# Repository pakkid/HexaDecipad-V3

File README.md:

# HexaDecipad-V3

**HexaDecipad-V3** is a custom-designed macropad built for **[Hack Club Stardance](https://stardance.hackclub.com/)**—a summer engineering program run by Hack Club in partnership with NASA, AMD, and GitHub. 

After running into some issues with the previous versions, Version 3 is redesigned from the ground up to be reliable and highly functional!

---

## Hardware Features

- **Microcontroller:** Seeed Studio XIAO (compatible with XIAO RP2040, SAMD21, etc.)
- **Keys:** 10x Cherry MX-compatible hotswap sockets (using `MX100H` footprints)
- **Rotary Encoders:** 2x Alps EC11-style rotary encoders with integrated push switches
- **Key Matrix Diodes:** 12x 1N4148 through-hole diodes (`DO-35` package)
- **PCB Design:** Fully designed in KiCad (files located in the `PCB/` directory)

---

## Repository Structure

- [`PCB/`](file:///home/pakkid/Documents/GitHub/HexaDecipad-V3/PCB/) — KiCad schematic (`.kicad_sch`), PCB layout (`.kicad_pcb`), and libraries.
- [`LICENSE`](file:///home/pakkid/Documents/GitHub/HexaDecipad-V3/LICENSE) — MIT License.

---

## Stardance YSWS
This project was shipped as part of **Hack Club's Stardance YSWS** ("You Ship, We Ship")

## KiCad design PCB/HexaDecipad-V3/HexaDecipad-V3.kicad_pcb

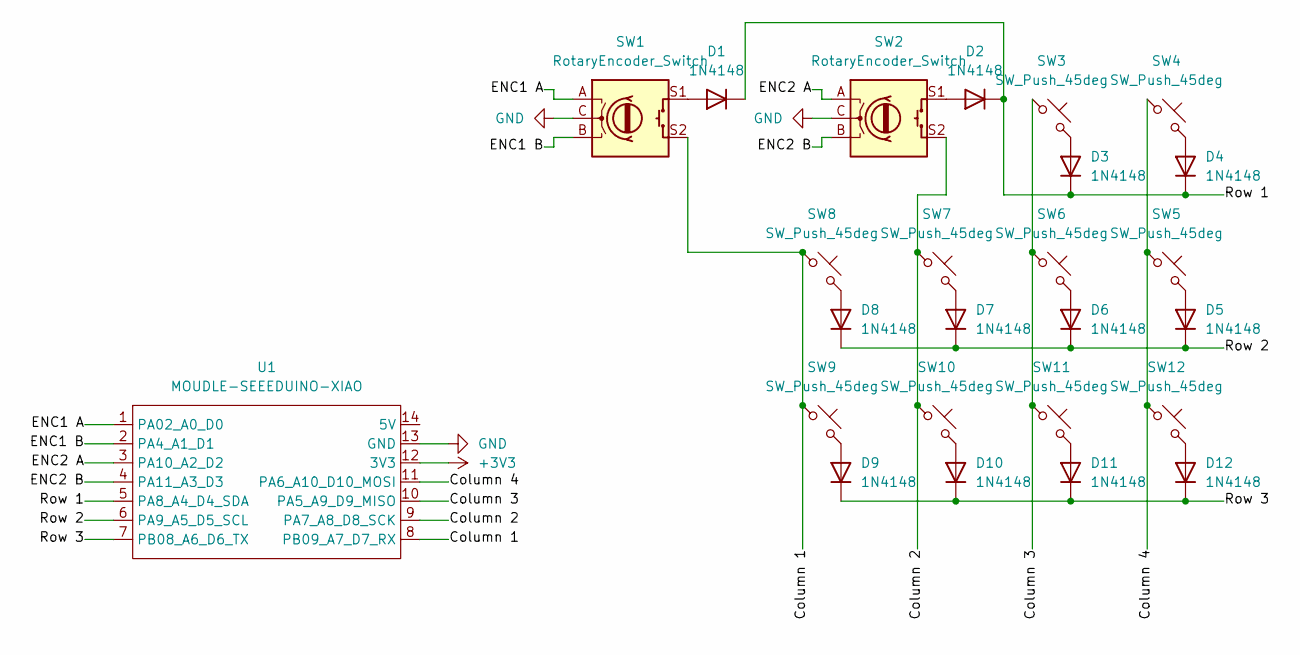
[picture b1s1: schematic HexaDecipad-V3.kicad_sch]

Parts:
D1, D2, D3, D4, D5, D6, D7, D8, D9, D10, D11, D12: 1N4148; D_DO-35_SOD27_P7.62mm_Horizontal
SW1, SW2: RotaryEncoder_Switch; RotaryEncoder_Alps_EC11E-Switch_Vertical_H20mm
SW3, SW4, SW5, SW6, SW7, SW8, SW9, SW10, SW11, SW12: SW_Push_45deg; MX100H
U1: MOUDLE-SEEEDUINO-XIAO; XIAO-Generic-Hybrid-14P-2.54-21X17.8MM

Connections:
+3V3: U1.12 (3V3)
/Column 1: SW1.S2, SW8.1, SW9.1, U1.8 (PB09_A7_D7_RX)
/Column 2: SW2.S2, SW7.1, SW10.1, U1.9 (PA7_A8_D8_SCK)
/Column 3: SW3.1, SW6.1, SW11.1, U1.10 (PA5_A9_D9_MISO)
/Column 4: SW4.1, SW5.1, SW12.1, U1.11 (PA6_A10_D10_MOSI)
/ENC1 A: SW1.A, U1.1 (PA02_A0_D0)
/ENC1 B: SW1.B, U1.2 (PA4_A1_D1)
/ENC2 A: SW2.A, U1.3 (PA10_A2_D2)
/ENC2 B: SW2.B, U1.4 (PA11_A3_D3)
/Row 1: D1.1 (K), D2.1 (K), D3.1 (K), D4.1 (K), U1.5 (PA8_A4_D4_SDA)
/Row 2: D5.1 (K), D6.1 (K), D7.1 (K), D8.1 (K), U1.6 (PA9_A5_D5_SCL)
/Row 3: D9.1 (K), D10.1 (K), D11.1 (K), D12.1 (K), U1.7 (PB08_A6_D6_TX)
GND: SW1.C, SW2.C, U1.13 (GND)
unnamed: D1.2 (A), SW1.S1
unnamed: D2.2 (A), SW2.S1
unnamed: D3.2 (A), SW3.2
unnamed: D4.2 (A), SW4.2
unnamed: D5.2 (A), SW5.2
unnamed: D6.2 (A), SW6.2
unnamed: D7.2 (A), SW7.2
unnamed: D8.2 (A), SW8.2
unnamed: D9.2 (A), SW9.2
unnamed: D10.2 (A), SW10.2
unnamed: D11.2 (A), SW11.2
unnamed: D12.2 (A), SW12.2

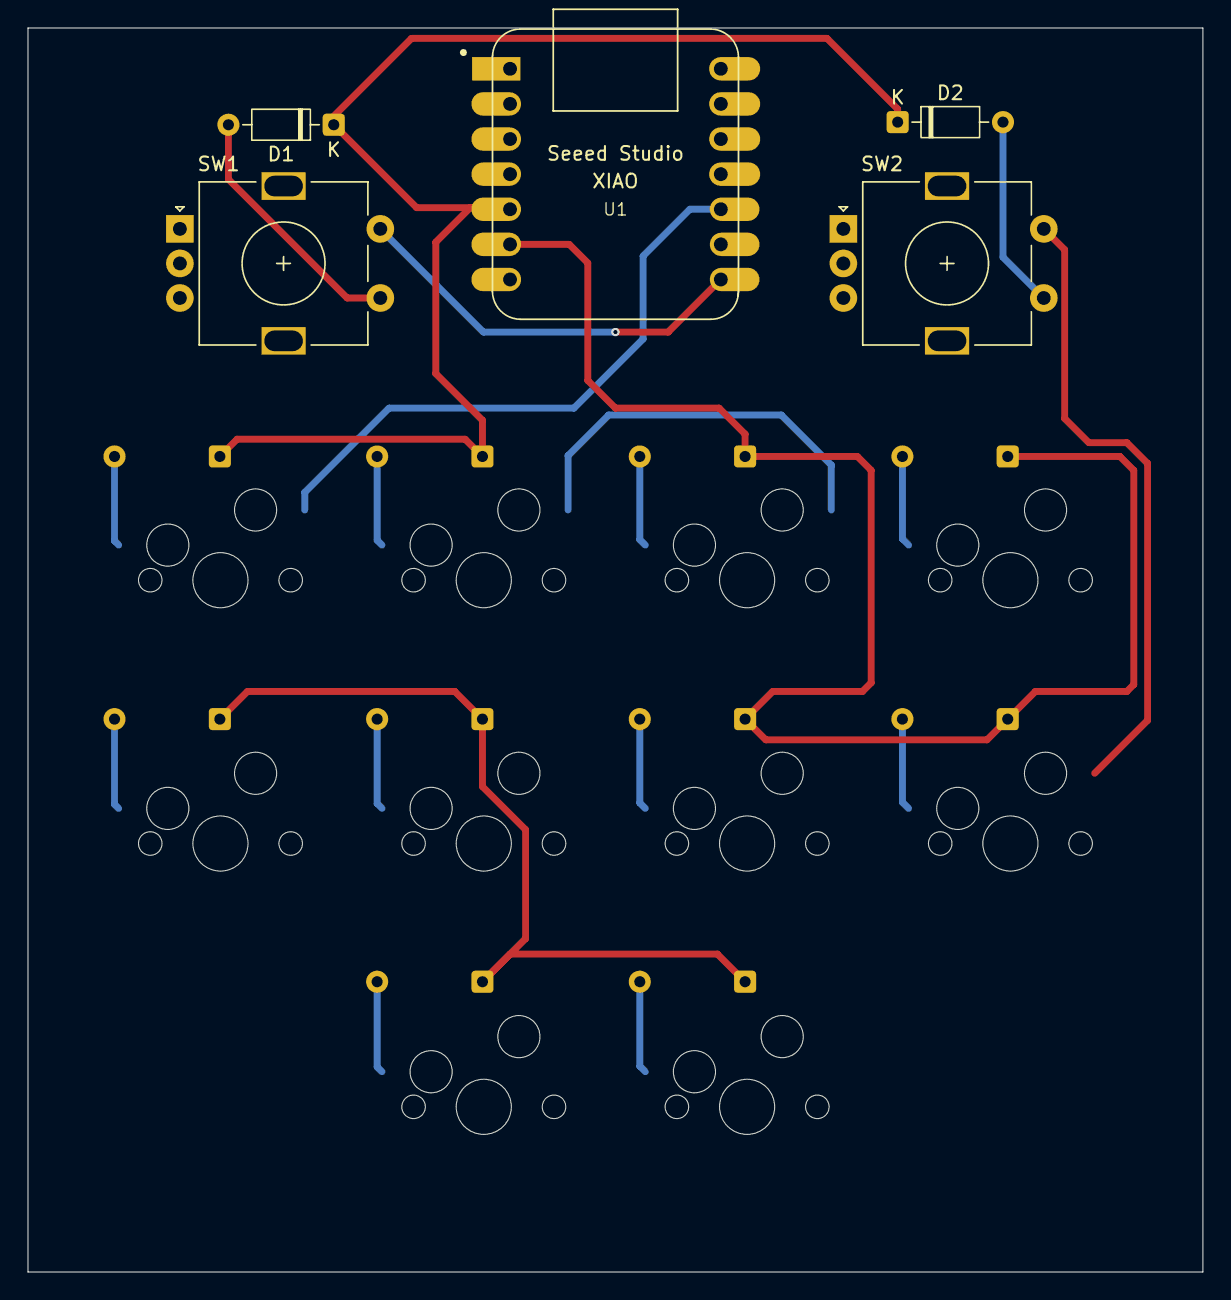
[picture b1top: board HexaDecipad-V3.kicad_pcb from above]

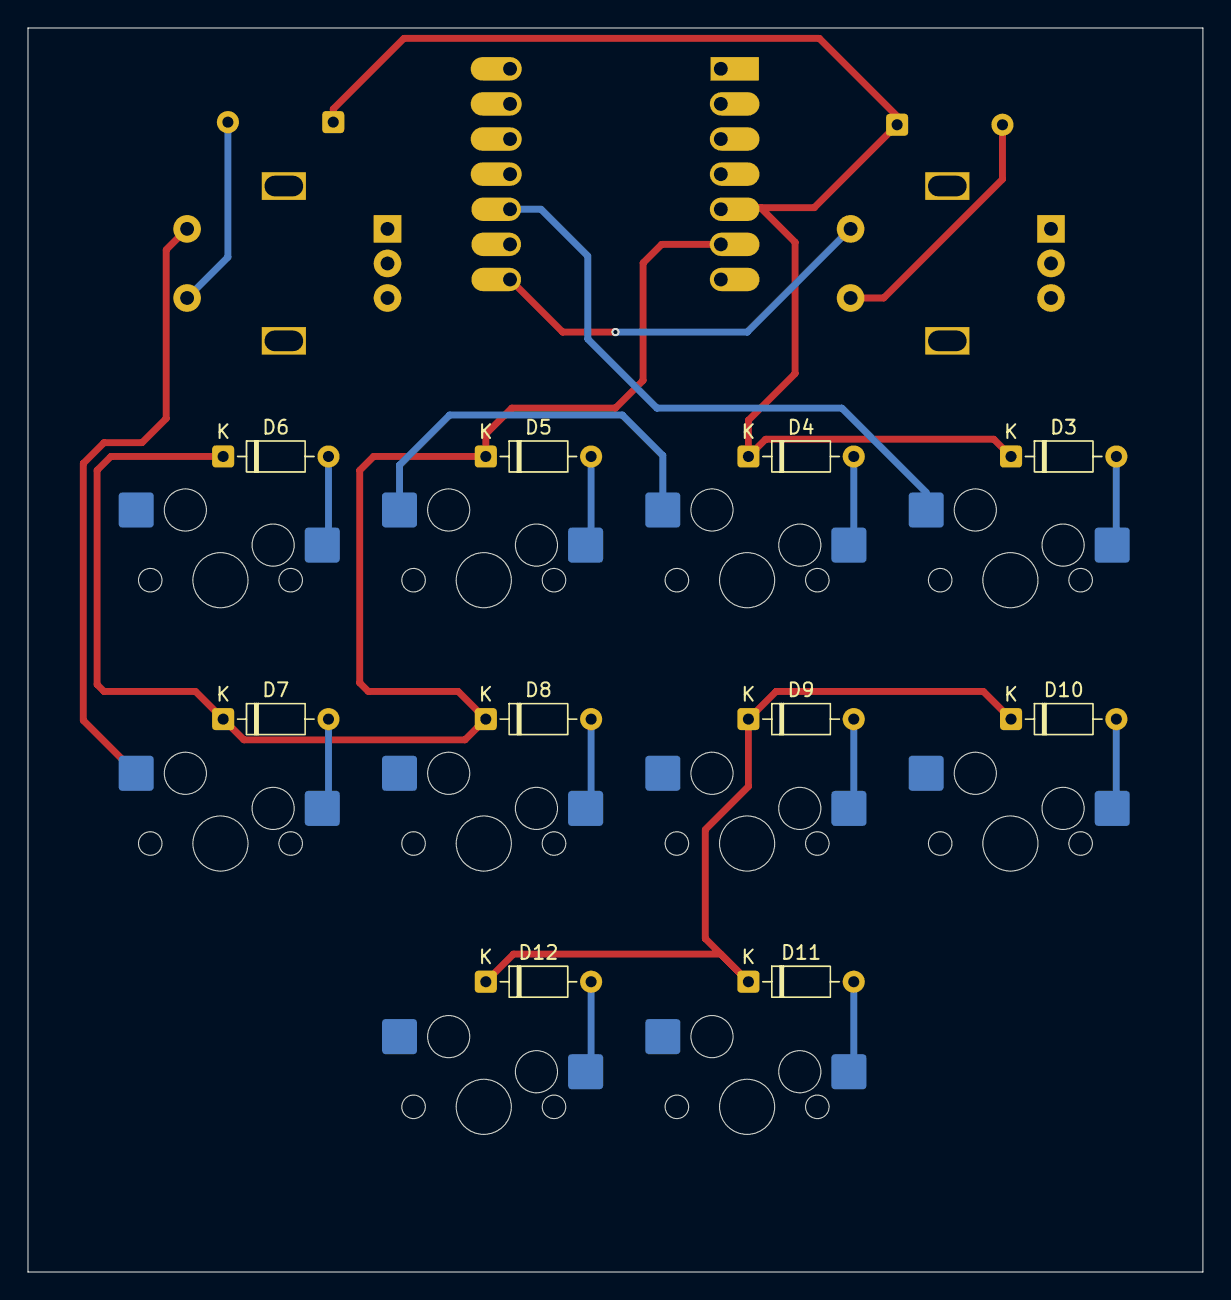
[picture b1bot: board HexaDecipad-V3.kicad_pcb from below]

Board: 2 copper layers, 85.0 x 90.0 mm, 25 parts (20 on the bottom side), 24 nets.

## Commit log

2026-06-09 uhhh yeah. upload everything.
2026-06-09 another thing
2026-06-09 what is this
2026-06-09 ummm idk. i trust gemini
2026-06-09 fix my stupid gitignore maybe
2026-06-10 pushing stuff
